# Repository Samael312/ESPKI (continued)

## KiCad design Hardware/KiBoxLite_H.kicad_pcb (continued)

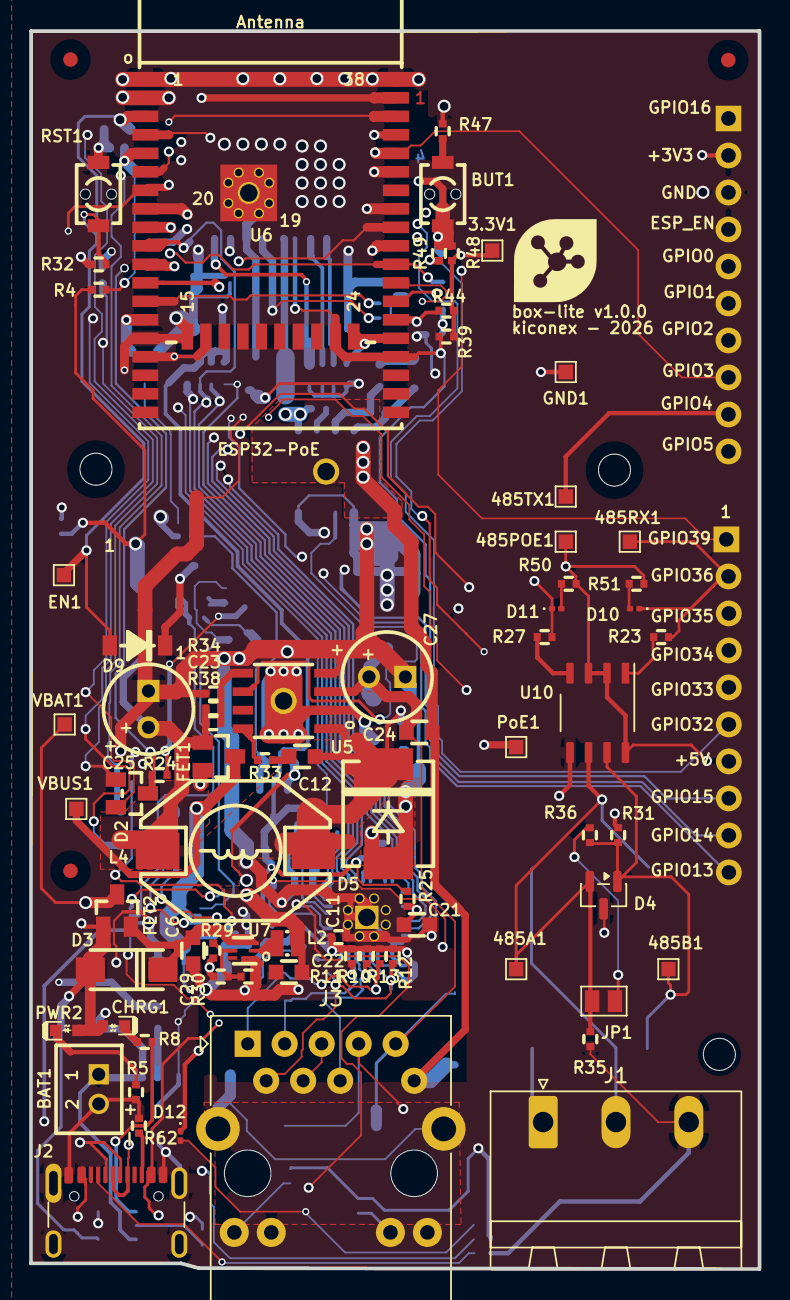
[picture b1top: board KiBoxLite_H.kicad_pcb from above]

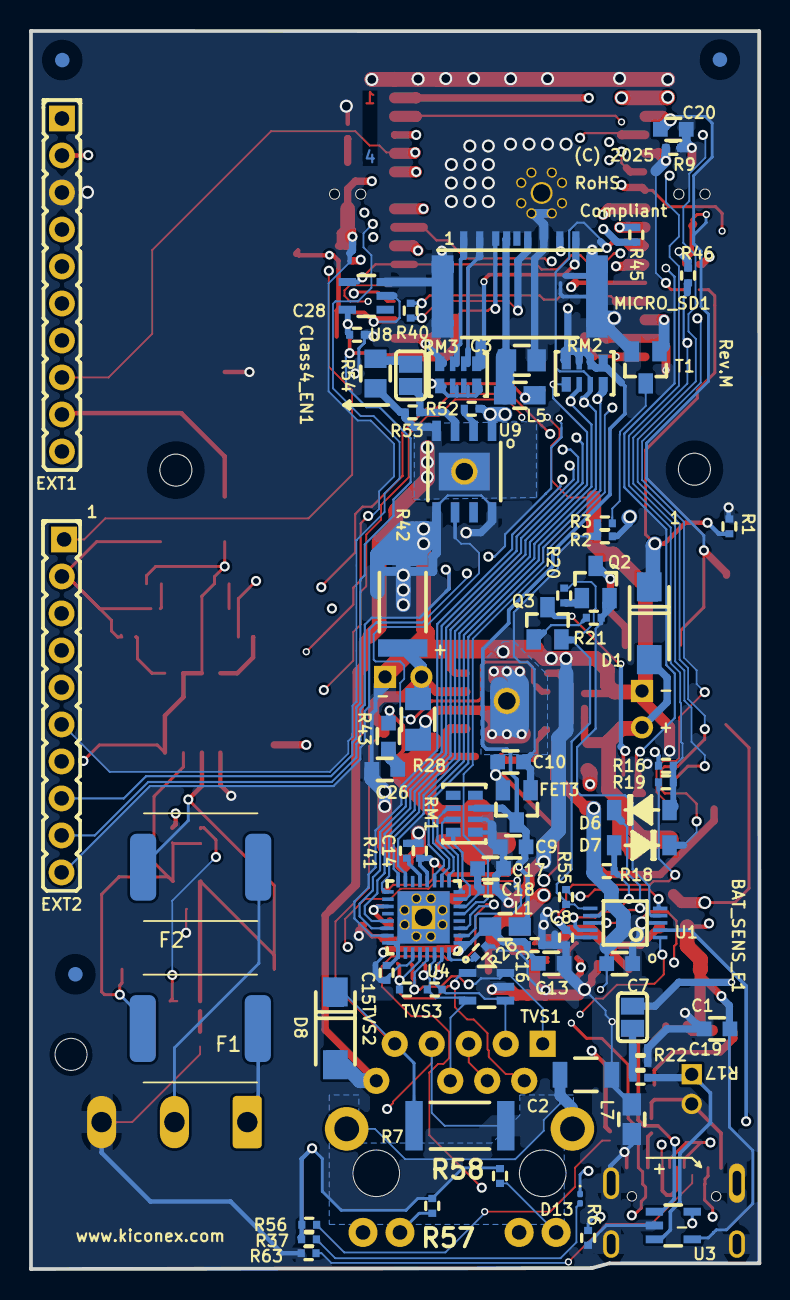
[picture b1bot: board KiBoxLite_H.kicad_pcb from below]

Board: 4 copper layers, 50.0 x 85.0 mm, 161 parts (80 on the bottom side), 106 nets.

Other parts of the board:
Logo: logo_ki_10x10mm

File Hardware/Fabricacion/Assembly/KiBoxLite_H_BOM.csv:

Component Count: 85;;;;;;;
;;;;;;;
Id;Designator;Footprint;Quantity;Value;Reference;Description;Attributes
1;3.3V1, 485A1, 485B1, 485POE1, 485RX1, 485TX1, EN1, GND1, PoE1, VBAT1, VBUS1;TestPoint_Pad_1.0x1.0mm;11;TestPoint;;;
2;BAT1;LIPO_BAT_VERTICAL_DW02S;1;DW02S;;;
3;BAT_SENS_E1;SJ;1;Opened;;;
4;BUT1, RST1;IT1185AU2_V2;2;IT1185AU2;IT1185AU2;Tactile Switch 2.0mm;
5;C1, C6, C7, C9, C10, C13, C22;C_0603_5MIL_DWS;7;22uF/6.3V/20%/X5R/C0603;C15850;22uF 6.3V 20% X5R 0603;
6;C2;C_1206_5MIL_DWS_ISO;1;1nF/2000V/10%/X7R/C1206;C441091;1nF 2000V 10% X7R 1206;
7;C3;C_0805_5MIL_DWS;1;47uF/6.3V/20%/X5R/C0805;C45304;47uF 6.3V 20% X5R 0805;
8;C8, C11, C14, C15, C16, C18;C_0402_5MIL_DWS;6;100nF/10V/20%/X5R/C04020;C1525;100nF 10V 10% X5R 0402;
9;C12, C24;C_0603_5MIL_DWS;2;100nF/100V/10%/X7R/C0603;C14663;100nF 100V 10% X7R 0603;
10;C17;C_0603_5MIL_DWS;1;2.2uF/6.3V/10%/X5R/C0603;C15849;2.2uF 10V 10% X5R 0603;
11;C19;C_0402_5MIL_DWS;1;1nF/50V/10%/X7R/C0402;C1523;1nF 50V 10% X7R 0402;
12;C20;C_0603_5MIL_DWS;1;1uF/10V/20%/X5R/C0603;C15849;1uF 10V 10% X5R 0603;
13;C21;C_0603_5MIL_DWS;1;10uF/6.3V/20%/X5R/C0603;C19702;10uF 10V 10% X5R 0603;DNP
14;C23;C_0402_5MIL_DWS;1;12pF/50V/5%/COG/C0402;C1547;12pF 50V 5% COG 0402;
15;C25;CPOL-RM2.5mm_6.3x11mm_PTH;1;470uF/10V/20%/Low_ESR/RM2.5/6.0x11mm;;;
16;C26;C_0603_5MIL_DWS;1;220pF/100V/C0603;C1593;220pF 100V 10% COG 0603;DNP
17;C27;CPOL-RM2.5mm_6.3x11mm_PTH;1;15uF/100V/20%/RM2.5/6.3x11mm(Farnell:1281844;1281844;Aluminum Cap 15uF 100V PTH;
18;C28;C_0402_5MIL_DWS;1;100nF/10V/20%/X5R/C04020;C1525;100nF 10V 10% X5R 0402;DNP
19;C29;C_0402_5MIL_DWS;1;120pF/50V/5%/C0G/C0402;C1548;120pF 50V 5% COG 0402;DNP
20;CHRG1;LED_0603_KA;1;LED/YELLOW/0603;C72038;LED Yellow 0603;
21;Class4_EN1;SJ;1;Closed;;;
22;D1, D3;SMA-KA;2;1N5822/SS34/SMA;SS34;Schottky Diode SMA;
23;D2;SOT23-3;1;BAT54C(SOT23-3;BAT54C;Schottky Barrier Diode SOT-23;
24;D4;SOT-23;1;SM712_SOT23;SM712;TVS Diode Array SOT-23;
25;D5;DO214AB(SMC)_1(K)-2(A);1;SS510/100V/5A/0.85V/DO214AB(SMC;SS510;Schottky Diode SMC;
26;D6, D7, D9;SOD-123_1C-2A_KA;3;1N5819S4(SOD-123;1N5819S4;Schottky Diode SOD-123;
27;D8;SMA-KA;1;SMAJ58A/SMA;SMAJ58A;TVS Diode SMA;
28;D10, D11, D12, D13;LED_0201_0603Metric;4;LED;C2286;LED 0603;
29;EXT1, EXT2;HN1x10;2;NS(HN1x10;;;
30;F1, F2;TS250;2;Polyfuse_Small;;;
31;FET1, FET2, FET3;SOT23;3;WPM2015-3/TR;WPM2015-3/TR;P-Channel MOSFET SOT-23;
32;FID1, FID2, FID3, FID4, FID5, FID6;Fiducial1x3;6;Fiducial;;;
33;J1;PhoenixContact_MSTBA_2,5_3-G_1x03_P5.00mm_Horizontal;1;Screw_Terminal_01x03;;;
34;J2;USB_C_Receptacle_GCT_USB4105-xx-A_16P_TopMnt_Horizontal;1;USB4105-GF-A-060;USB4105-GF-A-060;USB-C Connector 16-pin;
35;J3;RJ45_Abracon_ARJP11A-MA_Horizontal;1;RJ45_Abracon_ARJP11A-MASA-B-A-EMU2;ARJP11A-MASA-B-A-EMU2;RJ45 with Magnetics;
36;L1, L5, L7;L_0805_5MIL_DWS;3;FB0805/600R/2A;C1017;Ferrite Bead 0805;
37;L2;L_2016_MM;1;1.0uH/4.2A/DCR=35mR/20%/2.00x1.60x1.00mm/L2016(PIM201610-1R0MTS00;PIM201610-1R0MTS00;Inductor 2016 1.0uH;
38;L4;DBS135;1;33uH/2.1A/DCR=0.1R/20%/DBS135(PD3316MT330;PD3316MT330;Inductor 33uH;
39;MH1, MH2, MH3;NPTH_2.2mm;3;Mounting_Hole_NPTH;;;
40;MICRO_SD1;uSD(TFC-9P-1.xH(ATFFS150A01BR016));1;TFC-9P-1.7H(ATFFS150A01BR016;ATFFS150A01BR016;MicroSD Slot;
41;PWR2;LED_0603_KA;1;LED/RED/0603;C2286;LED Red 0603;
42;Q2, Q3;SOT23;2;BC817-40(SOT23;BC817-40;NPN Transistor SOT-23;
43;R1, R2, R6, R18, R19, R25, R32, R39, R48;R_0402_5MIL_DWS;9;10k/R0402;C25744;10k 1% 0402;
44;R3, R20, R21;R_0402_5MIL_DWS;3;1k/R0402;C21190;1k 1% 0402;
45;R4;R_0402_5MIL_DWS;1;47k/R0402;C25917;47k 1% 0402;
46;R5, R8, R41, R57, R58;R_0402_5MIL_DWS;5;2.2k/R0402;C25830;2.2k 1% 0402;
47;R7, R42;R_2512_MM_DWS;2;9.1k/R2512;;;
48;R9;R_0402_5MIL_DWS;1;100k/R0402;C25741;100k 1% 0402;
49;R10, R11, R12, R13;R_0402_5MIL_DWS;4;49.9R/1%/R0402;C25119;49.9R 1% 0402;
50;R16;R_0402_5MIL_DWS;1;10k/R0402;C25744;10k 1% 0402;DNP
51;R17, R22;R_0402_5MIL_DWS;2;470k/R0402;C25911;470k 1% 0402;
52;R23, R27;R_0402_5MIL_DWS;2;22R;C25092;22R 1% 0402;
53;R24, R46, R47;R_0402_5MIL_DWS;3;220R/R0402;C25080;220R 1% 0402;
54;R26;R_0402_5MIL_DWS;1;12.1k/1%/R0402;C21190;1k 1% 0402;
55;R28;R_1206_5MIL_DWS;1;0.03R/1%/R1206;C18924;Resistor 0.03R 1% 1206;
56;R29;R_0402_5MIL_DWS;1;220k/R0402;C25812;220k 1% 0402;
57;R30;R_0402_5MIL_DWS;1;49.9k/1%/R0402;C25785;49.9k 1% 0402;
58;R31, R35;R_0402_5MIL_DWS;2;220R;C25080;220R 1% 0402;
59;R33;R_0402_5MIL_DWS;1;4.7R/R0402;C25115;4.7R 1% 0402;
60;R34;R_0402_5MIL_DWS;1;5.23k/1%/R0402;C25890;5.23k 1% 0402;
61;R36;R_0402_5MIL_DWS;1;120R;C25070;120R 1% 0402;
62;R37, R50, R51, R56;R_0402_5MIL_DWS;4;2.2K;C25830;2.2k 1% 0402;
63;R38;R_0402_5MIL_DWS;1;30.1k/1%/R0402;C21190;1k 1% 0402;
64;R40;R_0402_5MIL_DWS;1;10R/R0402;C25068;10R 1% 0402;
65;R43;R_0603_5MIL_DWS;1;22R/R0603;;;DNP
66;R44, R49;R_0402_5MIL_DWS;2;R0402;;;DNP
67;R45;R_0402_5MIL_DWS;1;10R/R0402;C25068;10R 1% 0402;DNP
68;R52;R_0402_5MIL_DWS;1;24.9k/1%/R0402;C25769;24.9k 1% 0402;
69;R53;R_0402_5MIL_DWS;1;1.27k/1%/62.5mW/R0402;C25852;1.27k 1% 0402;
70;R54;R_0805_5MIL_DWS;1;66.5R/1%/125mW/R0805;C17772;Resistor 66.5R 1% 0805;DNP
71;R55;R_0402_5MIL_DWS;1;4.7k/R0402;C25900;4.7k 1% 0402;
72;R62, R63;R_0402_5MIL_DWS;2;5.1K;C21190;1k 1% 0402;
73;RM1, RM2, RM3;R_MATRIX_4;3;RA1206_(4X0603_4B8_2.2k;;;
74;T1;SOT23;1;LMUN2211LT1G(SOT-23;LMUN2211LT1G;NPN Digital Transistor SOT-23;
75;TVS1;SOT-23-5;1;ESDS314DBVR(SOT-23-5;ESDS314DBVR;4-Ch TVS Diode SOT-23-5;
76;TVS2, TVS3;D_0402_5MIL_DWS;2;GG0402052R542P;GG0402052R542P;ESD Suppressor 0402;DNP
77;U1;MSOP-10_Pitch-0.5mm_3.00x3.00x1.00mm;1;CH340X(MSOP-10;CH340X;USB to UART bridge MSOP-10;
78;U3;SOT-23-5;1;TP4054-42-SOT25-R(SOT23-5;TP4054-42-SOT25-R;Lipo Battery Charger SOT-25;
79;U4;QFN32_EP(33)_5.00x5.00x0.90mm_Pitch_0.50mm;1;LAN8710A-EZC(QFN32;LAN8710A-EZC;Ethernet PHY QFN-32;
80;U5;ESOIC-8;1;TX4138(ESOIC-8;TX4138;Flyback Switcher ESOIC-8;
81;U6;ESP32-WROOM-32E-N4;1;ESP32-WROOM-32E-N4;ESP32-WROOM-32E-N4;ESP32 Module 4MB Flash;
82;U7;SOT-563-6;1;TPS62A02ADRLR(SOT-563-6;TPS62A02ADRLR;Step-down converter SOT-563;
83;U8;SOT-23-5;1;SN74LVC1G04DBVR(SOT23-5;SN74LVC1G04DBVR;Single Inverter SOT-23-5;DNP
84;U9;ESOIC-8;1;TPS2378DDAR(HSOIC-8;TPS2378DDAR;PoE PD Interface ESOIC-8;
85;U10;MAX13487;1;MAX13487;MAX13487EESA+T;RS-485 Transceiver SOIC-8;

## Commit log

2026-03-11 build: Init
2026-03-11 build: Con test TLS WALL
2026-03-12 build: connected and subs
2026-03-13 build: entities
2026-03-17 build: buffer y logs memoria
2026-03-17 build: migracion hard
2026-03-20 build: parseo params
2026-03-20 build: Fase 1 lista
2026-03-27 Initial commit: KiBoxLite project modules
2026-03-27 Limpieza: aplicando .gitignore a archivos existentes
2026-04-06 build: USB-C Connected
2026-04-08 build: correcciones 261 errores remains
2026-04-08 build: correcciones 238 errores remains, huellas faltantes listas
2026-04-08 build: correcciones 160 errores remains, reduccion deL lagrimas
2026-04-09 build: correcciones, 7 errores remains
2026-04-10 build: 0 errores
2026-04-10 build: 0 errores 2
2026-04-10 build: 0 errores 1 aviso 4 exclusiones
2026-04-13 build: sch pdf
2026-04-13 build: Estructura organizada
2026-04-13 build: TestPoint logo
2026-04-15 build: .step
2026-04-15 build: carcasa iniciada
2026-04-20 build: fuse ts250
2026-04-20 build: fuse ts250 modelo 3d
2026-04-23 build: Cambio de puerto rs485
2026-04-24 build: Documentacion Hardware
2026-04-24 fix: act .gitignore
2026-04-24 Actualizado gitignore y dejada de rastrear carpeta build
2026-04-24 Actualizado gitignore 2
2026-04-27 act: .gitignore
2026-04-27 build: rj45 con leds
2026-04-28 build: correccion modbus
2026-05-05 build: optimizacion pcb
2026-05-05 build: gerbers pcb
2026-05-05 build: act .gitignore
2026-05-05 build: Lista y gerber
2026-05-06 build: Fabricacion
2026-05-07 build: gerbers pcb ACT
2026-05-08 build: funciona con modRs485
2026-05-08 build:RTU Listo
2026-05-08 build:Pub mod try
2026-05-08 updt: update .gitignore
2026-05-11 build: mejora parseo entities
2026-05-12 build: addr modbus
2026-05-12 build: addr modbus LISTO
2026-05-14 build: hash nivel 1 y 2
2026-05-14 build: report listo pend reorg
2026-05-15 build: Estrcutra organizada y report listos
2026-05-15 build: intento comandos
2026-05-15 build: depuracion comandos
2026-05-19 fix: set
2026-05-20 fix: set 2
2026-05-21 build: timer sampling modbus optimizado
2026-05-22 build: sampling cycles
2026-05-22 build: get por demanda casi listo
2026-05-22 build: get por demanda main, basic listo full desborda
2026-05-25 build: get por demanda main, basic listo full desbordada 2
2026-05-25 build: desbordamiento solucionado
2026-05-26 build: demand queue liberada
2026-05-27 build: set en queue
2026-05-27 build: log sampling
2026-05-27 build: todas las funciones operativas
2026-05-28 build: cache de pulling modbus
2026-05-28 build: hasheo nivel 3
2026-05-29 feat: packetizer en report
2026-06-02 build: packetizer
2026-06-03 fix: ntp sync
2026-06-03 fix: packetizer improved
2026-06-04 fix: depuracion dead code
2026-06-04 fix: optimizacion de queud
2026-06-05 fact: modularizacion parcial con error
2026-06-11 refact: error de desbordamiento
2026-06-11 build: tcp listo
2026-06-11 refact: limpieza logs
2026-06-12 refact: kx_modbus
2026-06-12 fix: CMakeLists
2026-06-12 build: .md modbus
2026-06-15 refact: modularizacion
2026-06-15 refact: dep logs
2026-06-15 fix: tcp error reports
2026-06-15 build: Readme.md
